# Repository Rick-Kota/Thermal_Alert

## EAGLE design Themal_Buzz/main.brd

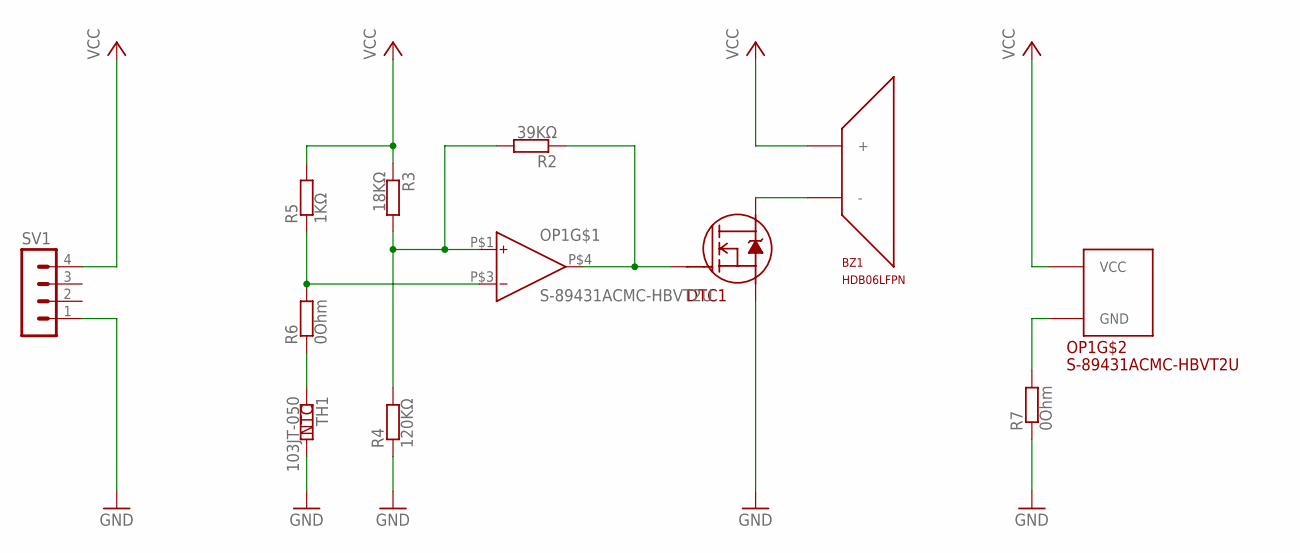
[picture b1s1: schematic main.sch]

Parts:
BZ1: HDB06LFPN; HDB06FLPN
DTC1: RT1P137P; SC-62
OP1: S-89431ACMC-HBVT2U; SOT-23-5
R2: 39KΩ; MF1/4
R3: 18KΩ; MF1/4
R4: 120KΩ; MF1/4
R5: 1KΩ; MF1/4
R6, R7: 0Ohm; MF1/4
SV1: MA04-1
TH1: 103JT-050; JT-W

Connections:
GND: DTC1.E (S), R4.P$2 (2), R7.P$2 (2), SV1.1, TH1.P$1 (1)
unnamed: DTC1.B (G), OP1.P$4 (OUT), R2.P$2 (2)
unnamed: OP1.P$3 (IN-), R5.P$2 (2), R6.P$1 (1)
unnamed: BZ1.P$2 (-), DTC1.C1 (D), DTC1.C2 (D)
unnamed: R6.P$2 (2), TH1.P$2 (2)
unnamed: OP1.P$2 (GND), R7.P$1 (1)
unnamed: OP1.P$1 (IN+), R2.P$1 (1), R3.P$1 (1), R4.P$1 (1)
VCC: BZ1.P$1 (+), OP1.P$5 (VCC), R3.P$2 (2), R5.P$1 (1), SV1.4

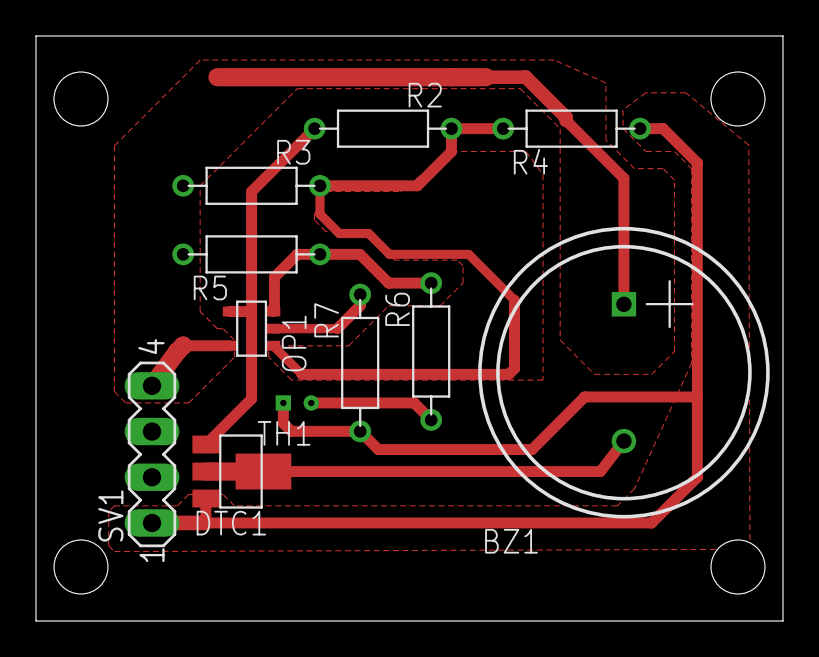
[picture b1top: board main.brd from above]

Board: 2 copper layers, 41.5 x 32.5 mm, 11 parts (0 on the bottom side), 8 nets.

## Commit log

2018-06-09 基本構成の完成
    回路図およびパターンデータの完成
    ヒステリシスの設定(抵抗値)は未設定
2018-06-12 抵抗値の設定完了
    各抵抗値の設定完了
